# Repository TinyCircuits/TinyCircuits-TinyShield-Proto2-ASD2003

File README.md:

# TinyCircuits TinyShield Proto2 Board
# ASD2003 Rev3

These are the design files for the TinyCircuits ASD2003 Rev 3 PCB.  This is a Tiny shield board (Square Version, 20mm x 20mm, or Circular 20mm diameter) that has some of the shield signals brought out to 0.1" spaced holes. 

Format is in Cadsoft Eagle format - Eagle version 6.2 was used for the original design.

For more infomation on this, check out the product page at Tiny-Circuits.com:: https://tiny-circuits.com/tiny-shield-proto-board-2.html

#License:

Design by TinyCircuits.
All design files are released under the Creative Commons Attribution Share-Alike 3.0 License, see the following link for details: http://creativecommons.org/licenses/by-sa/3.0

All text above must be included in any redistribution or derived design

This project uses designs and concepts developed as part of the Arduino project and the LilyPad project.  The TinyCircuits design files themselves (schematics, PCB and libraries) are not directly derived from these works' design files and have been created new, however the concepts and basic architecture behind the TinyDuino and TinyLily products are derived and we thank the hard work of the organizations below for their contributions to open-source hardware:
  
Original Arduino Uno Design by Team Arduino

LilyPad Arduino Design by Leah Buechley and Sparkfun Electronics

Please support the open-source hardware community

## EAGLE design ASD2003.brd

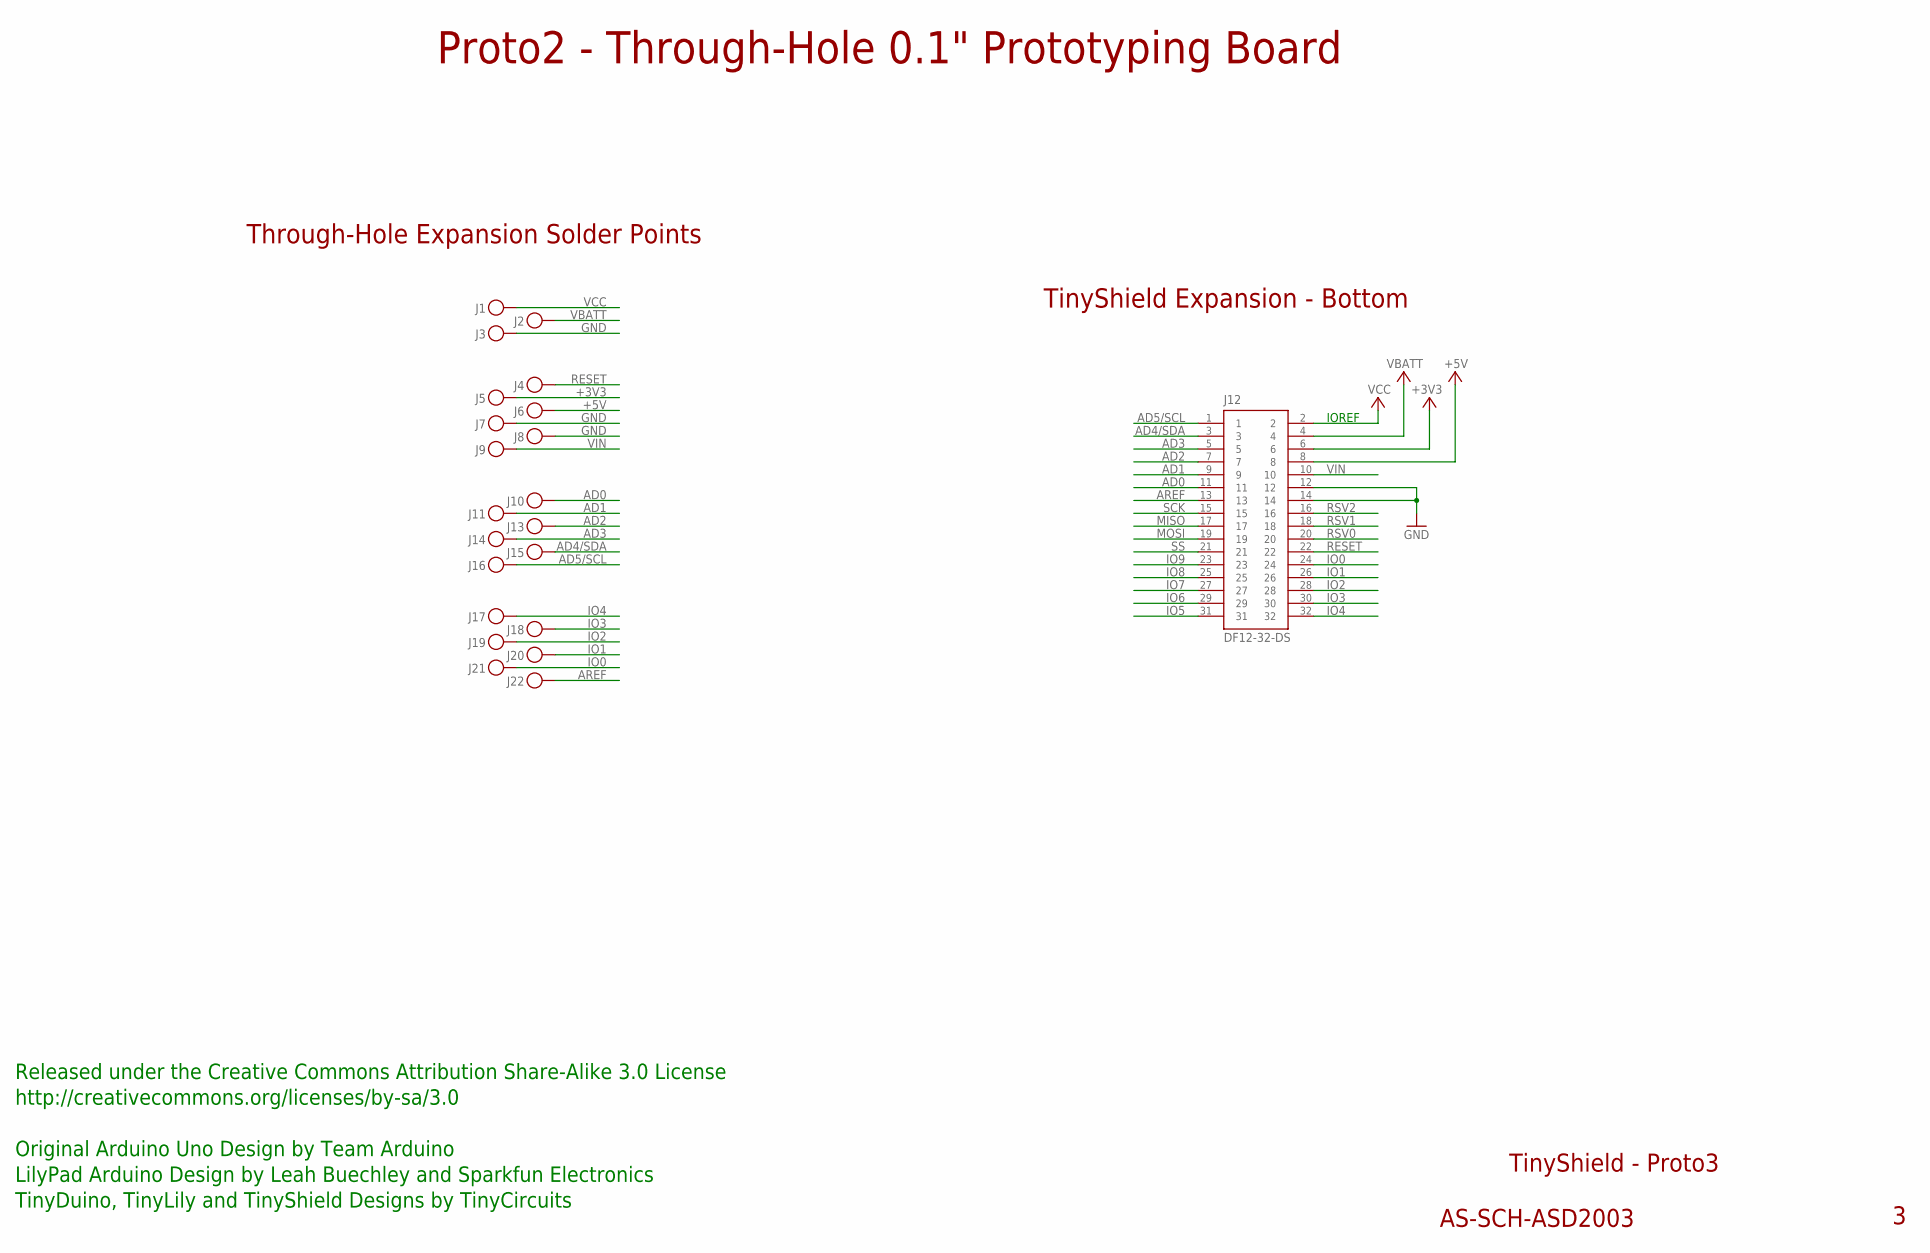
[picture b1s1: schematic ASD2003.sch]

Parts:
J1, J2, J3, J4, J5, J6, J7, J8, J9, J10, J11, J13, J14, J15, J16, J17, J18, J19, J20, J21, J22: PIN_1X.1"1; 1X.1"_2; PARTNO COPPER
J12: DF12-32-DS; PARTNO AS-ITM-00012

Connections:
+3V3: J5.1, J12.6
+5V: J6.1, J12.8
AD0: J10.1, J12.11
AD1: J11.1, J12.9
AD2: J12.7, J13.1
AD3: J12.5, J14.1
AD4/SDA: J12.3, J15.1
AD5/SCL: J12.1, J16.1
AREF: J12.13, J22.1
GND: J3.1, J7.1, J8.1, J12.12, J12.14
IO0: J12.24, J21.1
IO1: J12.26, J20.1
IO2: J12.28, J19.1
IO3: J12.30, J18.1
IO4: J12.32, J17.1
IO5: J12.31
IO6: J12.29
IO7: J12.27
IO8: J12.25
IO9: J12.23
MISO: J12.17
MOSI: J12.19
RESET: J4.1, J12.22
RSV0: J12.20
RSV1: J12.18
RSV2: J12.16
SCK: J12.15
SS: J12.21
VBATT: J2.1, J12.4
VCC: J1.1, J12.2
VIN: J9.1, J12.10

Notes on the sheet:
TinyShield Expansion - Bottom
TinyShield - Proto3
AS-SCH-ASD2003
IOREF
Released under the Creative Commons Attribution Share-Alike 3.0 License
http://creativecommons.org/licenses/by-sa/3.0
LilyPad Arduino Design by Leah Buechley and Sparkfun Electronics
TinyDuino, TinyLily and TinyShield Designs by TinyCircuits
Through-Hole Expansion Solder Points
Original Arduino Uno Design by Team Arduino
Proto2 - Through-Hole 0.1" Prototyping Board

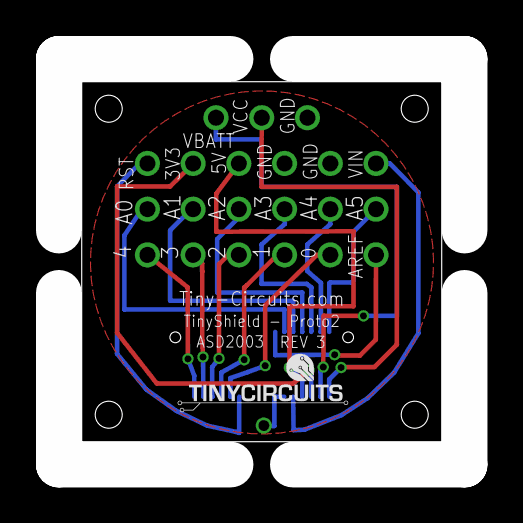
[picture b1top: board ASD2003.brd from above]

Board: 2 copper layers, 20.0 x 20.0 mm, 23 parts (1 on the bottom side), 19 nets.

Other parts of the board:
U$1: DOCFIELD-TINYCIRCUITS-PCB

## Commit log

2013-06-30 Updated project link
2013-12-24 Updated to Rev 3
2013-12-26 Fixed incorrect schematic label
2014-08-24 Updated Link
